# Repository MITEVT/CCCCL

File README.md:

CCCCL
=====

Computer Controlled Constant Current Load

-Attiny85 branch

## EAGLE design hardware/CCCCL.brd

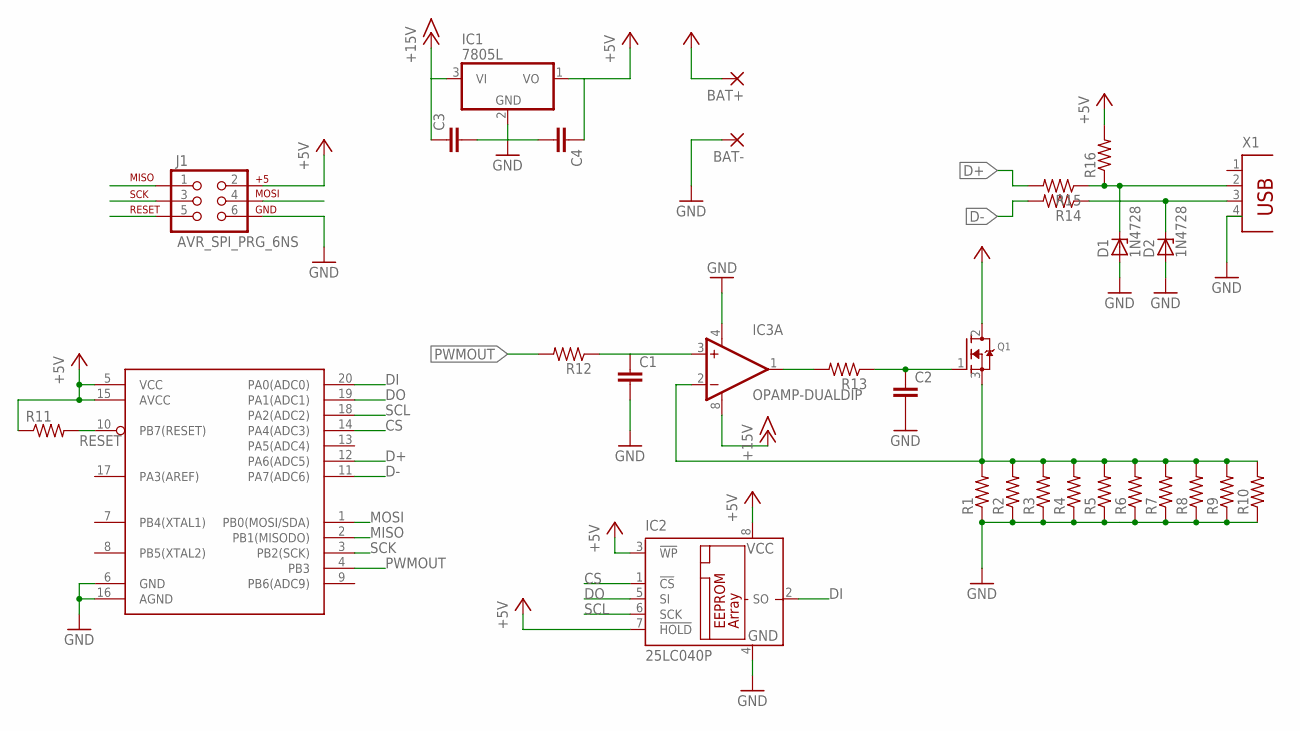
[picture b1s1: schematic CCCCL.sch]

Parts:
BAT+: 3,17/1,3
BAT-: 3,17/1,3
C1, C2: C-EU025-040X050; C025-040X050
C3, C4: C2,5-3; C2.5-3
D1, D2: 1N4728; DO41Z10
IC1: 7805L; TO92
IC2: 25LC040P; DIL8
IC3: OPAMP-DUALDIP; DIP08
J1: AVR_SPI_PRG_6NS; 2X3-NS
Q1: MOSFET-NGDS_TO220V; TO220V
R1, R2, R3, R4, R5, R6, R7, R8, R9, R10, R11, R12, R13, R14, R15, R16: R-US_0309/12; 0309/12
U$1: ATTINY261ADIP; DIL20
X1: PN87520

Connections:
+5V: C4.1, IC1.1 (VO), IC2.3 (!WP), IC2.7 (!HOLD), IC2.8 (VCC), J1.2, R11.1, R16.2, U$1.5 (VCC), U$1.15 (AVCC)
+15V: C3.1, IC1.3 (VI), IC3.8 (V+)
CS: IC2.1 (!CS), U$1.14 (PA4(ADC3))
D+: R15.2, U$1.12 (PA6(ADC5))
D-: R14.2, U$1.11 (PA7(ADC6))
DI: IC2.2 (SO), U$1.20 (PA0(ADC0))
DO: IC2.5 (SI), U$1.19 (PA1(ADC1))
GND: BAT-.1, C1.2, C2.2, C3.2, C4.2, D1.A, D2.A, IC1.2 (GND), IC2.4 (GND), IC3.4 (V-), J1.6, R1.1, R2.1, R3.1, R4.1, R5.1, R6.1, R7.1, R8.1, R9.1, R10.1, U$1.6 (GND), U$1.16 (AGND), X1.4
MISO: J1.1, U$1.2 (PB1(MISODO))
MOSI: J1.4, U$1.1 (PB0(MOSI/SDA))
unnamed: IC3.1 (OUT), R13.2
unnamed: IC3.2 (-IN), Q1.3 (S), R1.2, R2.2, R3.2, R4.2, R5.2, R6.2, R7.2, R8.2, R9.2, R10.2
unnamed: D2.C, R14.1, X1.3
unnamed: C1.1, IC3.3 (+IN), R12.1
unnamed: C2.1, Q1.1 (G), R13.1
unnamed: D1.C, R15.1, R16.1, X1.2
PWMOUT: R12.2, U$1.4 (PB3)
RESET: J1.5, R11.2, U$1.10 (PB7(RESET))
SCK: J1.3, U$1.3 (PB2(SCK))
SCL: IC2.6 (SCK), U$1.18 (PA2(ADC2))
VB: BAT+.1, Q1.2 (D)

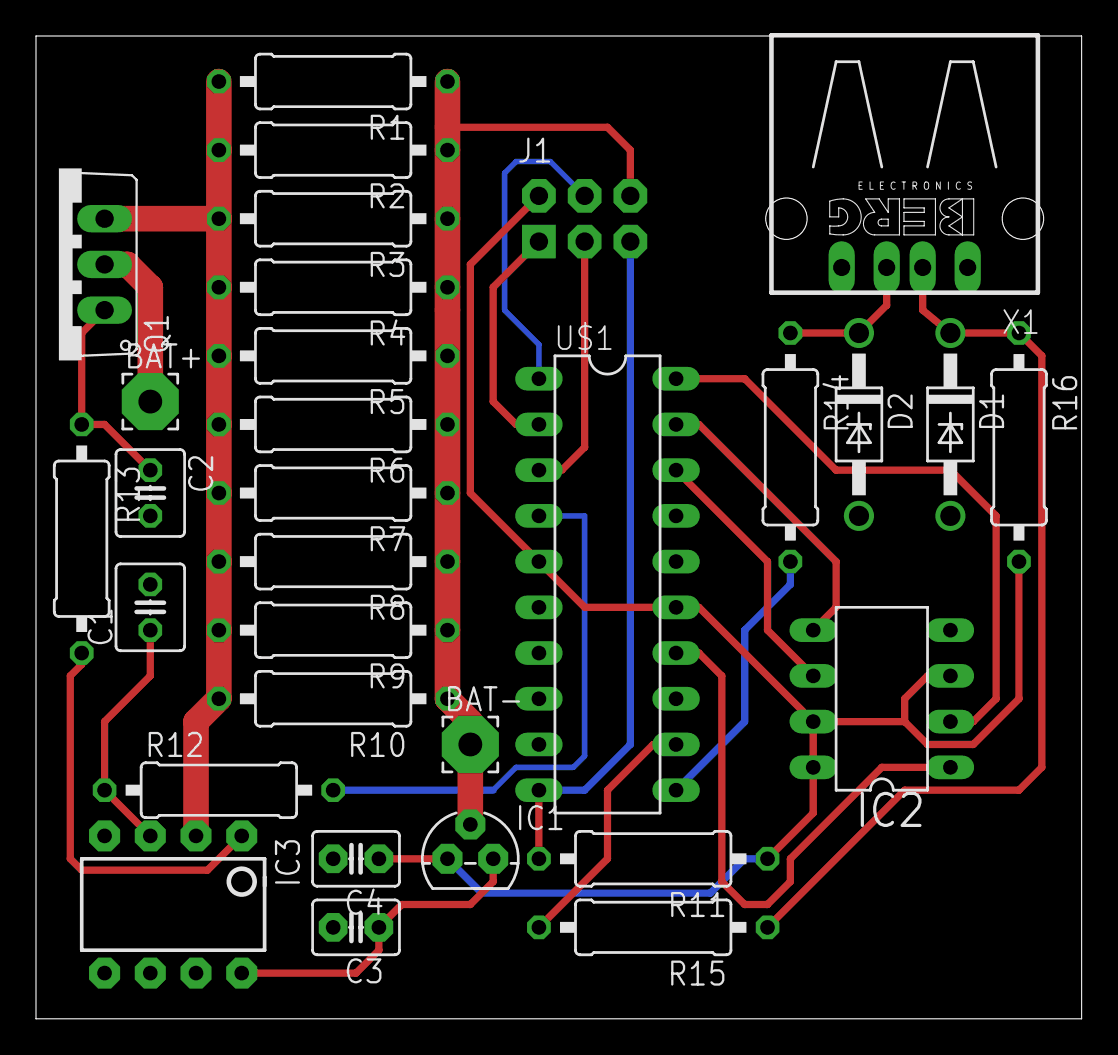
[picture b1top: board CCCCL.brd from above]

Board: 2 copper layers, 58.1 x 54.6 mm, 31 parts (0 on the bottom side), 21 nets.

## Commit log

2013-10-28 added innitial schematic and modified git ignore
    Added eagley-thigns to gitignore and created a directory structure for
    foftware and hardware
2013-10-28 added the 10th resistor and battery power supply connection
2013-11-01 added a tiny85 uC for controll
    added uC and ISP, LPF for both PWM gen and feedback compensation
2013-11-01 innitial firmware commit
2013-11-01 changed PWM pin for output to analog
2013-11-01 modified Makefile for tiny85 and updated gitignore for list files
2013-11-01 Added Code to ATtiny code
    Creates a PWM signal at a 100kHz frequency
2013-11-02 Fixed improper register values
2013-11-02 Added checks to setPulseWidth()
2013-11-03 innitial commit for tiny261 added USB circuit
2013-11-04 added SPI eeprom for data storage
2013-11-09 corrected pulsewidth setting method
2013-11-16 Routed board, separated ground planes
2013-11-20 fixed up power routing

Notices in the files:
parts and their libraries:
SparkFun-AnalogIC: Licensing: CC v3.0 Share-Alike You are welcome to use this library for commercial purposes.
